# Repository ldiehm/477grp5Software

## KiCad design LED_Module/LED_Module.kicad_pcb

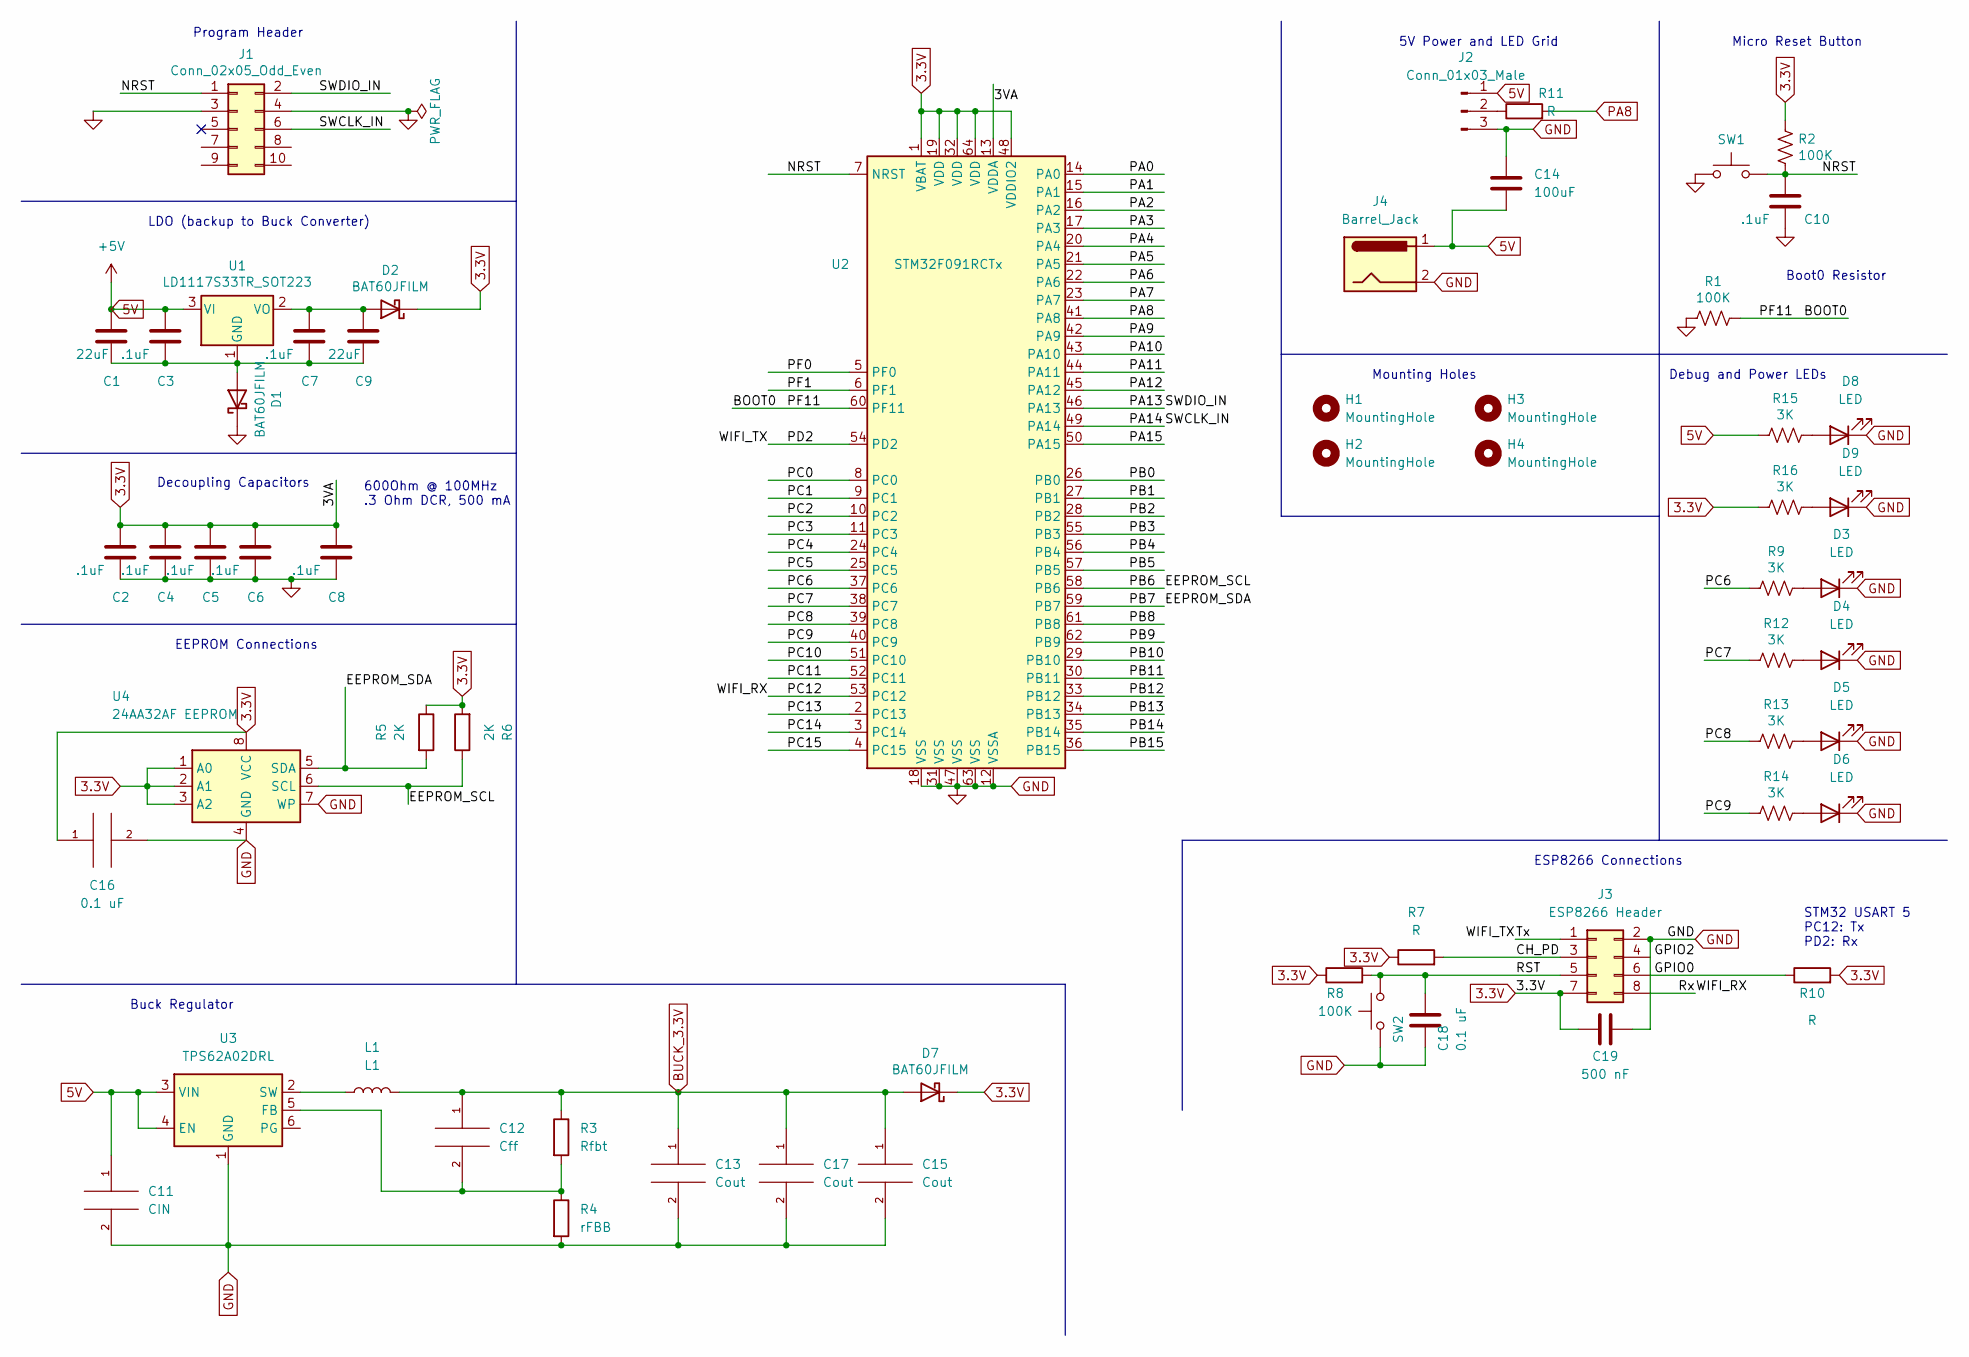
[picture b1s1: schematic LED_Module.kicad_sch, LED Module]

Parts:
C1, C9: 22uF; C_0805_2012Metric_Pad1.18x1.45mm_HandSolder
C2, C3, C4, C5, C6, C7, C8, C10: .1uF; C_0805_2012Metric_Pad1.18x1.45mm_HandSolder
C11: CIN; C_0805_2012Metric_Pad1.18x1.45mm_HandSolder
C12: Cff; C_0402_1005Metric_Pad0.74x0.62mm_HandSolder
C13, C15, C17: Cout; C_1206_3216Metric_Pad1.33x1.80mm_HandSolder
C14: 100uF
C16, C18: 0.1 uF; C_0805_2012Metric_Pad1.18x1.45mm_HandSolder
C19: 500 nF; C_0805_2012Metric_Pad1.18x1.45mm_HandSolder
D1, D2, D7: BAT60JFILM; D_SOD-323
D3, D4, D5, D6, D8, D9: LED; LED_0805_2012Metric_Pad1.15x1.40mm_HandSolder
H1, H2, H3, H4: MountingHole; MountingHole_3.2mm_M3
J1: Conn_02x05_Odd_Even; IDC-Header_2x05_P2.54mm_Vertical
J2: Conn_01x03_Male
J3: ESP8266 Header; PinHeader_2x04_P2.54mm_Vertical
J4: Barrel_Jack
L1: L1; L_0603_1608Metric_Pad1.05x0.95mm_HandSolder
R1, R2, R8: 100K; R_0805_2012Metric_Pad1.20x1.40mm_HandSolder
R3: Rfbt; R_0805_2012Metric_Pad1.20x1.40mm_HandSolder
R4: rFBB; R_0805_2012Metric_Pad1.20x1.40mm_HandSolder
R5, R6: 2K; R_0805_2012Metric_Pad1.20x1.40mm_HandSolder
R7, R10, R11: R; R_0805_2012Metric_Pad1.20x1.40mm_HandSolder
R9, R12, R13, R14, R15, R16: 3K; R_0805_2012Metric_Pad1.20x1.40mm_HandSolder
SW1, SW2: SW_Push; SW_SPST_PTS645
U1: LD1117S33TR_SOT223; SOT-223-3_TabPin2
U2: STM32F091RCTx; LQFP-64_10x10mm_P0.5mm
U3: TPS62A02DRL; SOT-563
U4: 24AA32AF EEPROM; DIP-8_W7.62mm_Socket

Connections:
3.3V: C2.1, C4.1, C5.1, C6.1, C8.1, C16.1, C19.2, D2.1 (K), D7.1 (K), J3.7 (3.3V), R2.1, R5.1, R6.2, R7.1, R8.1, R10.2, R16.2, U2.1 (VBAT), U2.13 (VDDA), U2.19 (VDD), U2.32 (VDD), U2.48 (VDDIO2), U2.64 (VDD), U4.1 (A0), U4.2 (A1), U4.3 (A2), U4.8 (VCC)
5V: C1.1, C3.1, C11.1, C14.2, J2.1, J4.1, R15.2, U1.3 (VI), U3.3 (VIN), U3.4 (EN)
/BOOT0: R1.1, U2.60 (PF11)
/CH_PD: J3.3 (CH_PD), R7.2
/EEPROM_SCL: R6.1, U2.58 (PB6), U4.6 (SCL)
/EEPROM_SDA: R5.2, U2.59 (PB7), U4.5 (SDA)
/GPIO0: J3.6 (GPIO0), R10.1
/NRST: C10.1, J1.1, R2.2, SW1.2, U2.7 (NRST)
/PA0: U2.14 (PA0)
/PA1: U2.15 (PA1)
/PA2: U2.16 (PA2)
/PA3: U2.17 (PA3)
/PA4: U2.20 (PA4)
/PA5: U2.21 (PA5)
/PA6: U2.22 (PA6)
/PA7: U2.23 (PA7)
/PA9: U2.42 (PA9)
/PA10: U2.43 (PA10)
/PA11: U2.44 (PA11)
/PA12: U2.45 (PA12)
/PA13: J1.2, U2.46 (PA13)
/PA14: J1.6, U2.49 (PA14)
/PA15: U2.50 (PA15)
/PB0: U2.26 (PB0)
/PB1: U2.27 (PB1)
/PB2: U2.28 (PB2)
/PB3: U2.55 (PB3)
/PB4: U2.56 (PB4)
/PB5: U2.57 (PB5)
/PB8: U2.61 (PB8)
/PB9: U2.62 (PB9)
/PB10: U2.29 (PB10)
/PB11: U2.30 (PB11)
/PB12: U2.33 (PB12)
/PB13: U2.34 (PB13)
/PB14: U2.35 (PB14)
/PB15: U2.36 (PB15)
/PC0: U2.8 (PC0)
/PC1: U2.9 (PC1)
/PC2: U2.10 (PC2)
/PC3: U2.11 (PC3)
/PC4: U2.24 (PC4)
/PC5: U2.25 (PC5)
/PC6: R9.2, U2.37 (PC6)
/PC7: R12.2, U2.38 (PC7)
/PC8: R13.2, U2.39 (PC8)
/PC9: R14.2, U2.40 (PC9)
/PC10: U2.51 (PC10)
/PC11: U2.52 (PC11)
/PC12: J3.8 (Rx), U2.53 (PC12)
/PC13: U2.2 (PC13)
/PC14: U2.3 (PC14)
/PC15: U2.4 (PC15)
/PD2: J3.1 (Tx), U2.54 (PD2)
/PF0: U2.5 (PF0)
/PF1: U2.6 (PF1)
/RST: C18.1, J3.5 (RST), R8.2, SW2.2
BUCK_3.3V: C12.1, C13.1, C15.1, C17.1, D7.2 (A), L1.2, R3.1
GND: C2.2, C4.2, C5.2, C6.2, C8.2, C10.2, C11.2, C13.2, C14.1, C15.2, C16.2, C17.2, C18.2, C19.1, D1.1 (K), D3.1 (K), D4.1 (K), D5.1 (K), D6.1 (K), D8.1 (K), D9.1 (K), J1.3, J1.4, J2.3, J3.2 (GND), J4.2, R1.2, R4.2, SW1.1, SW2.1, U2.12 (VSSA), U2.18 (VSS), U2.31 (VSS), U2.47 (VSS), U2.63 (VSS), U3.1 (GND), U4.4 (GND), U4.7 (WP)
unnamed: C1.2, C3.2, C7.2, C9.2, D1.2 (A), U1.1 (GND)
unnamed: C7.1, C9.1, D2.2 (A), U1.2 (VO)
unnamed: C12.2, R3.2, R4.1, U3.5 (FB)
unnamed: D3.2 (A), R9.1
unnamed: D4.2 (A), R12.1
unnamed: D5.2 (A), R13.1
unnamed: D6.2 (A), R14.1
unnamed: D8.2 (A), R15.1
unnamed: D9.2 (A), R16.1
unnamed: J2.2, R11.1
unnamed: L1.1, U3.2 (SW)
PA8: R11.2, U2.41 (PA8)

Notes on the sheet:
Micro Reset Button
EEPROM Connections
Mounting Holes
STM32 USART 5 PC12: Tx PD2: Rx
5V Power and LED Grid
Program Header
600Ohm @ 100MHz .3 Ohm DCR, 500 mA
Decoupling Capacitors
ESP8266 Connections
Debug and Power LEDs
Boot0 Resistor
Buck Regulator
LDO (backup to Buck Converter)

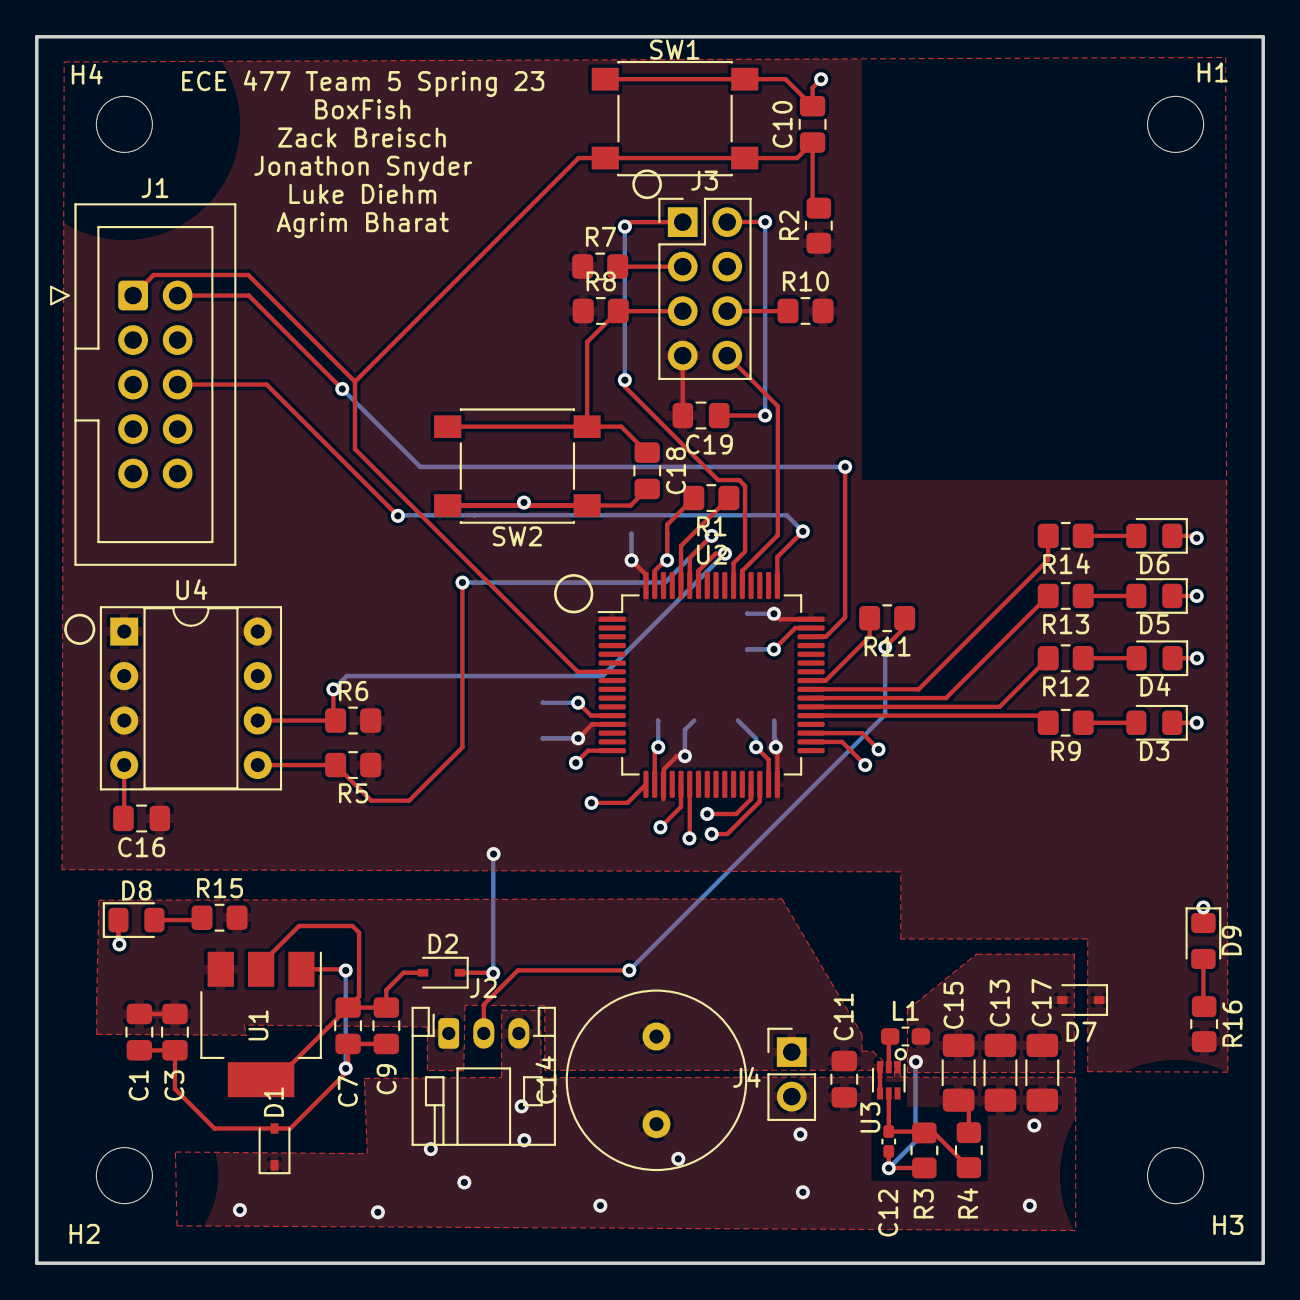
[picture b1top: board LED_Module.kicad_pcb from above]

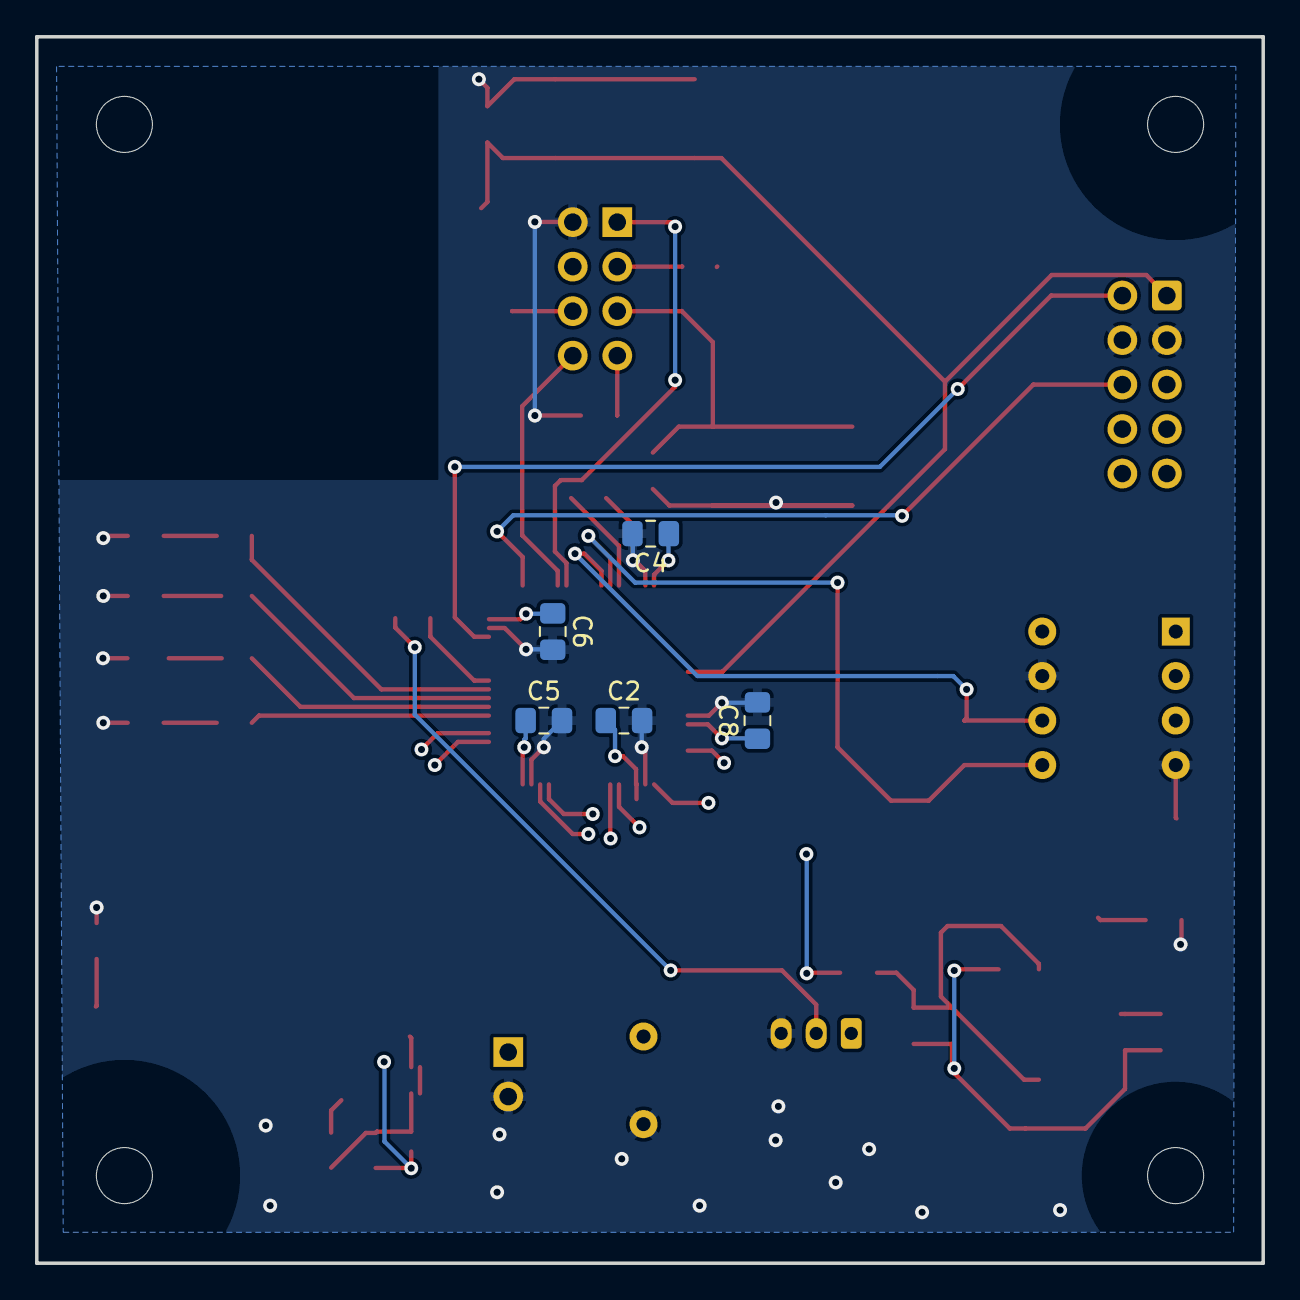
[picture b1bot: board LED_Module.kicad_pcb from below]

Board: 2 copper layers, 70.0 x 70.0 mm, 59 parts (5 on the bottom side), 31 nets.

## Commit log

2023-01-25 Add files via upload
    Stuff for USART testing
2023-01-26 Update main.c
    I (jonathon) added this under lukes account
2023-01-30 Flashing LEDs with unique indices works
2023-02-08 Upload KiCad Schematic
2023-02-08 Added ESP32 Code for TCP Access Point
2023-02-09 Buck Converter and Wifi schematic
2023-02-14 EEPROM Schematic, Decoupling routing, Buck Layout
2023-02-15 Revision to Buck Layout
2023-02-17 Systems laid out and 3.3V connected
2023-02-20 Power and ground planes plus complete routing
2023-02-21 Added bulk capacitor, diode, and some extra vias
2023-03-01 PCB design updated for week 8 design review
2023-03-01 Design Review Design
2023-03-01 Wednesday Morning Design Review Updates
2023-03-07 Final PCB Design used in order from PCB Way
2023-03-08 added BLE code file for phone
2023-03-08 added code for a large input buffer
2023-03-22 updated cohesive bluetooth + WiFi code
2023-03-29 Added timer6 IRQ
2023-04-12 Lab 0 for reference
2023-04-12 Delete ble_test.py
    Old code, no longer needed
2023-04-12 Update ble.py
    Works with APP now
2023-04-12 Added rx event handler to build array of bytes
2023-04-13 Receiving data from esp32. Debug in progress on transferdata funct
2023-04-13 Added code to handle buffers
2023-04-13 Works in debugger and fixed clock
2023-04-17 Added 'K' terminating character to data packet
2023-04-17 Code works on dev board
    This code runs fine on the dev board but not ours
2023-04-17 This code runs on the dev board but not ours
2023-04-17 Code runs on dev board but not ours
2023-04-19 Updated IP's to work with both displays
    This code correctly sends to both displays. If it doesn't work, try adjusting the IP addresses.
2023-04-19 Code works with multiple boards, power reset is good
2023-04-27 This should be the final version of the stm32 code
2023-04-27 Upload for archive
2023-04-27 renamed folders
